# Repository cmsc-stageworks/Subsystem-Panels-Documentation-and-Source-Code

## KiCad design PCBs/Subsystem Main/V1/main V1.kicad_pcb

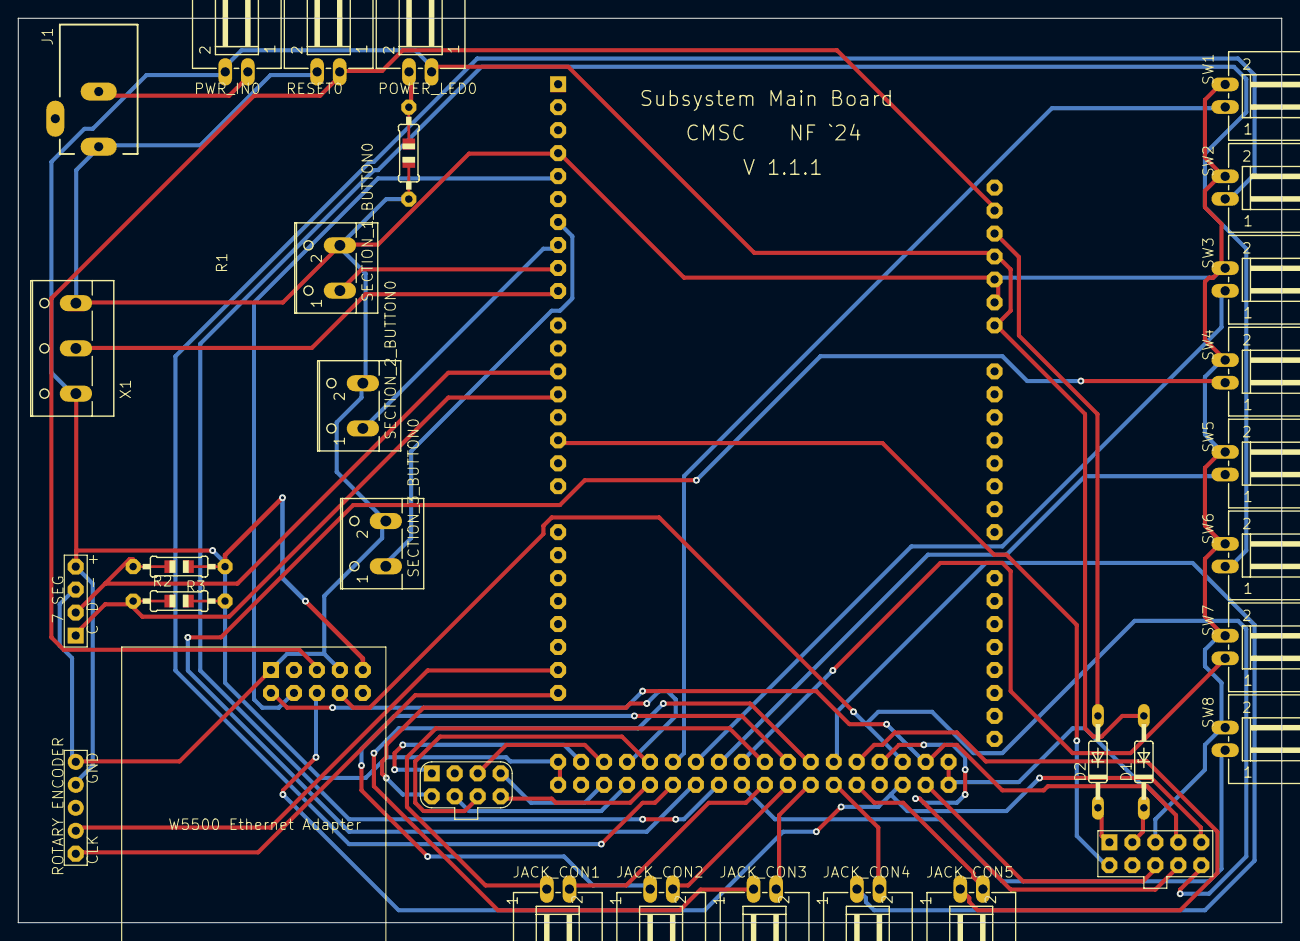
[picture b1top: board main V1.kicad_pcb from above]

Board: 2 copper layers, 139.7 x 100.0 mm, 32 parts (0 on the bottom side), 50 nets.

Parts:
D1, D2: 1N821; DO35Z10_210
J1: DCJ0303_154
JACK_CON1, JACK_CON2, JACK_CON3, JACK_CON4, JACK_CON5: L02P_123
POWER_LED0: L02P_123
PWR_IN0: L02P_123
R1: 100 Ohm; 0805-THM_420
R2, R3: 4.7K Ohm; 0805-THM_420
RESET0: L02P_123
SECTION_1_BUTTON0, SECTION_2_BUTTON0, SECTION_3_BUTTON0: W237-102_195
SW1, SW2, SW3, SW4, SW5, SW6, SW7, SW8: L02P_123
U$1: ARDUINO_MEGAMIRROR; ARDUINO_MEGA_MIRROR
U$2: 7_SEG_DISPLAY
U$3: SPI_HEADERSPI_HEADER_RIBBON_CONNECTOR; SPI_HEADER_RIBBON_CONNECTOR
U$4: BUTTON_GRID_HEADER; BUTTON_GRID_HEADER_RIBBON_CONNECTOR
U$5: ROTARY_ENCODER
U$6: ETHERNET_ADAPTER
X1: W237-103_195

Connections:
3V3: D2.A, U$1.3V3
5V: D1.A, POWER_LED0.1, PWR_IN0.2, R2.2, R3.1, U$1.5V@1, U$1.5V@2, U$1.5V@3, U$1.VIN, U$2.VCC, U$5.+, U$6.5V, X1.1
D2: U$1.D2, U$3.SPKR
D21: U$1.D21, U$5.CLK
D29: U$1.D29, U$4.PD
D48: U$1.D48, U$3.SD_CS
D53: U$1.D53, U$3.TFT_CS
GND: J1.1, R1.2, RESET0.2, SECTION_1_BUTTON0.2, SECTION_2_BUTTON0.2, SECTION_3_BUTTON0.2, SW1.2, SW2.2, SW3.2, SW4.2, SW5.2, SW6.2, SW7.2, SW8.2, U$1.GND@1, U$1.GND@2, U$1.GND@3, U$1.GND@4, U$1.GND@5, U$2.GND, U$3.GND, U$5.GND, U$6.GND@1, U$6.GND@2, X1.3
MISO: U$1.D50, U$3.MISO, U$6.MISO
MOSI: U$1.D51, U$3.MOSI, U$6.MOSI
unnamed: POWER_LED0.2, R1.1
unnamed: SW1.1, U$1.D30
unnamed: SW2.1, U$1.D31
unnamed: SW3.1, U$1.D32
unnamed: SW4.1, U$1.D33
unnamed: SW5.1, U$1.D34
unnamed: SW6.1, U$1.D35
unnamed: SW7.1, U$1.D36
unnamed: SW8.1, U$1.D37
unnamed: JACK_CON1.1, U$1.D38
unnamed: JACK_CON1.2, U$1.D39
unnamed: JACK_CON2.1, U$1.D40
unnamed: JACK_CON2.2, U$1.D41
unnamed: JACK_CON3.1, U$1.D42
unnamed: JACK_CON3.2, U$1.D43
unnamed: JACK_CON4.1, U$1.D44
unnamed: JACK_CON4.2, U$1.D45
unnamed: JACK_CON5.1, U$1.D46
unnamed: JACK_CON5.2, U$1.D47
unnamed: R2.1, U$1.D4, U$2.CLK
unnamed: R3.2, U$1.D5, U$2.DIO
unnamed: U$1.D28, U$4.PC
unnamed: U$1.D27, U$4.PB
unnamed: U$1.D26, U$4.PA
unnamed: U$1.D25, U$4.P4
unnamed: U$1.D24, U$4.P3
unnamed: U$1.D23, U$4.P2
unnamed: U$1.D22, U$4.P1
unnamed: U$1.D49, U$3.TFT_DC
unnamed: D2.C, U$3.3V3
unnamed: D1.C, U$3.5V
unnamed: U$1.D20, U$5.DT
unnamed: U$1.D8, X1.2
unnamed: SECTION_1_BUTTON0.1, U$1.D9
unnamed: SECTION_2_BUTTON0.1, U$1.D10
unnamed: SECTION_3_BUTTON0.1, U$1.D11
unnamed: U$1.D13, U$6.SCS
RAW_IN: J1.3, PWR_IN0.1
RESET: RESET0.1, U$1.RESET, U$6.RST
SCK: U$1.D52, U$3.SCK, U$6.SCLK
